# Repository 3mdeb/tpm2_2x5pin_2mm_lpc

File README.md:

# TPM2 module schematics

TPM2 module PCB project for platforms with 2x5 pin, 2mm pitch LPC header was
created for the Librebox platform under contract work from Libretrend company.

## Description

Trusted Platform Module compatible with 2x5p LPC header (populated on Librebox
platform) can be used in:

* disk encryption
* password protection
* platform integrity and other security issues

TPM module for Librebox features:

* TPM SLB9665TT20FW561XUMA1
* Operating voltage 3-3.3V
* Meeting Intel TXT, Microsoft Windows and Google Chromebook certification
  criteria for successful platform qualification
* True Random Number Generator (TRNG)
* Full personalization with Endorsement Key (EK) and EK certificate
* Supports the LPC interface

## Pinout

The pin layout is unique therefore users of other platforms should first make
sure that the pinout corresponds to the one from the image below:

## License

* Hardware is licensed under [CERN license](LICENSE.txt)
* Documentation is licensed under [CC BY-SA license](https://creativecommons.org/licenses/by-sa/2.0/)

## Where can I buy this product?

If you are not the enthusiast of DYI, then the plug and play product can be
bought in the:

* [Libretrend shop](https://libretrend.com/specs/librebox)
* [3mdeb shop](https://shop.3mdeb.com/product/tpm2-module-for-librebox/)

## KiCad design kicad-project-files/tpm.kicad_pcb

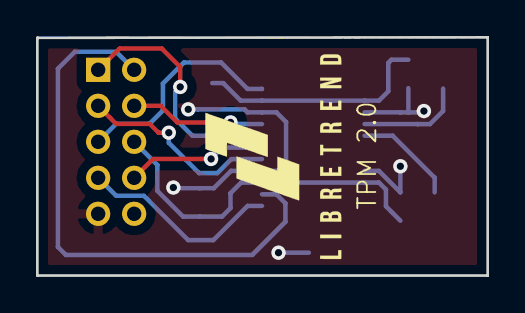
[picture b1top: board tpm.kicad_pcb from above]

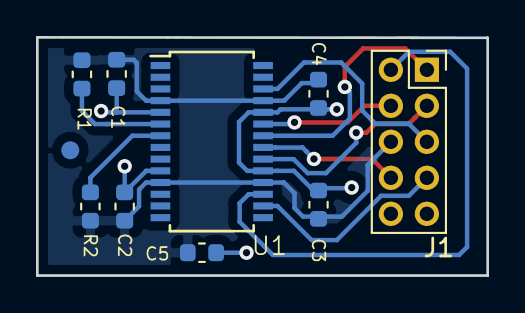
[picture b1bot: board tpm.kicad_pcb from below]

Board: 2 copper layers, 25.0 x 13.2 mm, 9 parts (9 on the bottom side), 11 nets.

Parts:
C1, C2, C3, C4: 100nF; C_0603_1608Metric
C5: 1uF; C_0603_1608Metric
J1: SLB9665 header; PinSocket_2x05_P2.00mm_Vertical
R1, R2: 10k; R_0603_1608Metric
U1: SLB9665; TSSOP-28_4.4x9.7mm_P0.65mm

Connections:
+3V3: C1.1, C2.1, C3.1, C4.1, C5.1, J1.9, U1.5, U1.10, U1.19, U1.24
GND: C1.2, C2.2, C3.2, C4.2, C5.2, J1.6, R1.1, R2.1, U1.4, U1.11, U1.18, U1.25
LAD0: J1.5, U1.26
LAD1: J1.4, U1.23
LAD2: J1.3, U1.20
LAD3: J1.2, U1.17
LCLK: J1.8, U1.21
LFRAME#: J1.1, U1.22
unnamed: R1.2, U1.6
unnamed: R2.2, U1.7
RST#: J1.7, U1.16

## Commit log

2018-09-24 Created initial version of the LPC bus
2018-10-12 Changed: size of the Libretrend logo
2018-10-22 Shorted +3v3 pins
2020-04-14 README.md: update description
2020-04-14 add LICENSE.txt file
2020-04-14 add tpm2_2x5pin_2mm_lpc.pdf file
2020-04-15 README.md: update shop link and pinout information
2020-04-30 README.md: add components licensing
2020-04-30 README.md: change grammar
